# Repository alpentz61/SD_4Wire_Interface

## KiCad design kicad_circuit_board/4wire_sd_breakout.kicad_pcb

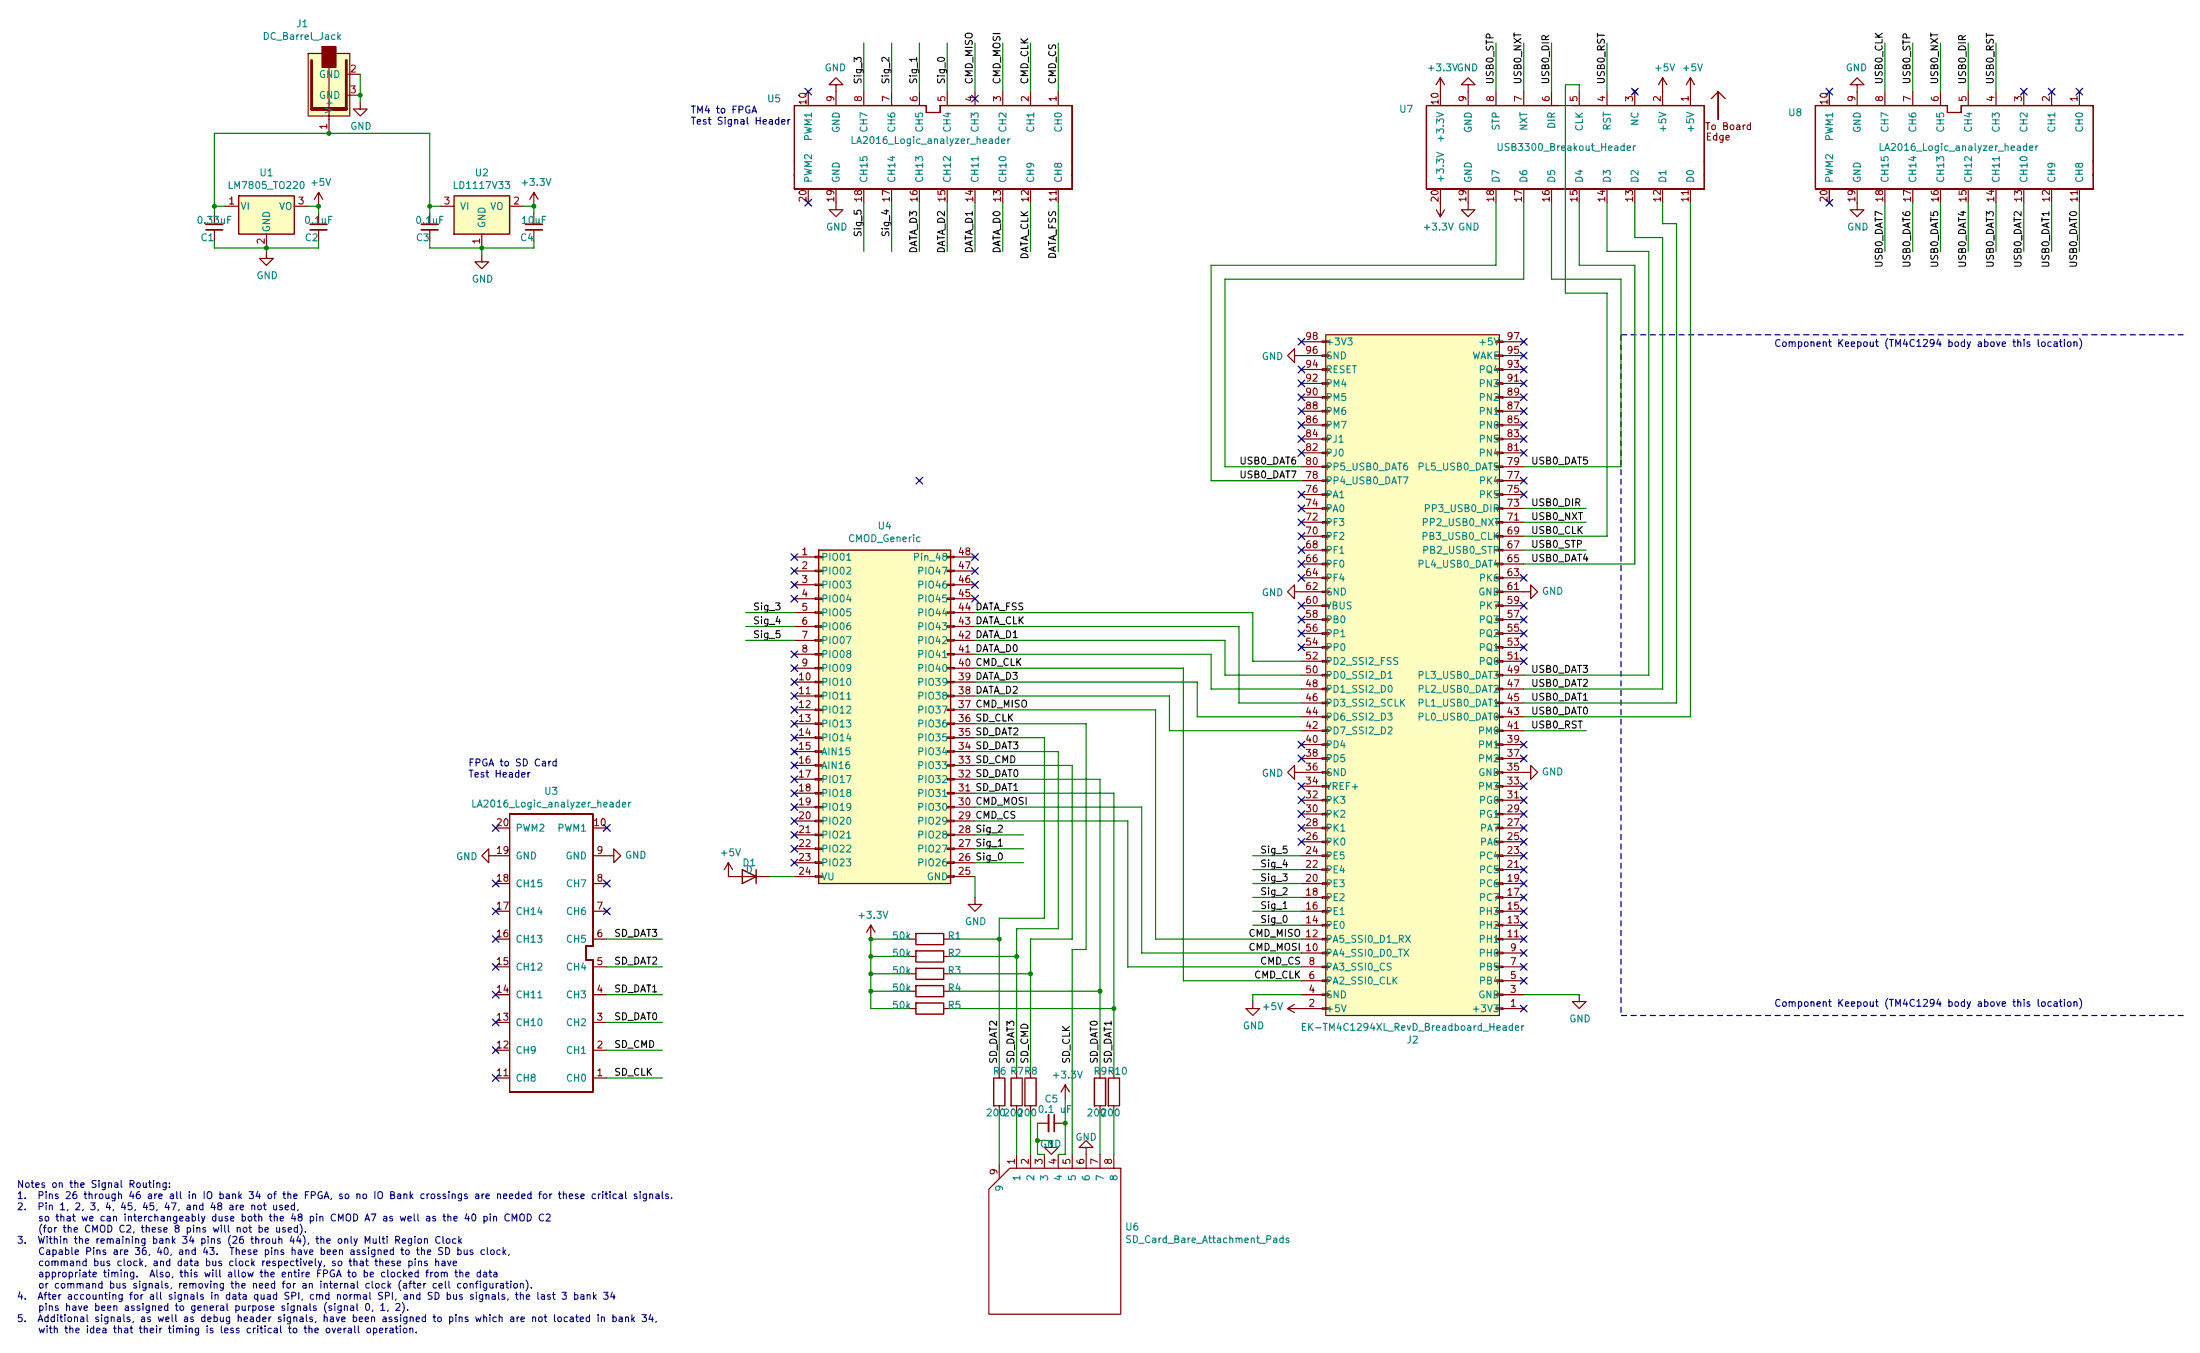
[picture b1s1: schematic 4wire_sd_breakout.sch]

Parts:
C1: 0.33uF; C_0603_1608Metric_Pad1.08x0.95mm_HandSolder
C2, C3: 0.1uF; C_0603_1608Metric_Pad1.08x0.95mm_HandSolder
C4: 10uF; C_0603_1608Metric_Pad1.08x0.95mm_HandSolder
C5: 0.1 uF; C_0603_1608Metric_Pad1.08x0.95mm_HandSolder
D1: D; D_A-405_P12.70mm_Horizontal
J1: DC_Barrel_Jack; DC_Barrel_Adapter
J2: EK-TM4C1294XL_RevD_Breadboard_Header
R1, R2, R3, R4, R5: 50k; R_0603_1608Metric_Pad0.98x0.95mm_HandSolder
R6, R7, R8, R9, R10: 200; R_0603_1608Metric_Pad0.98x0.95mm_HandSolder
U1: LM7805_TO220; TO-220-3_Vertical
U2: LD1117V33; TO-220-3_Vertical
U3, U5, U8: LA2016_Logic_analyzer_header; LA2016_Logic_Analyzer_Connector
U4: CMOD_Generic
U6: SD_Card_Bare_Attachment_Pads; SD_Card_Bare_Wire_Attachment_Pads
U7: USB3300_Breakout_Header; LA2016_Logic_Analyzer_Connector

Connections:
+3V3: C4.2, C5.1, R1.2, R2.2, R3.2, R4.2, R5.2, U2.2 (VO), U6.4, U7.10 (+3.3V), U7.20 (+3.3V)
+5V: C2.2, D1.2 (A), J2.2 (+5V), U1.3 (VO), U7.1 (+5V), U7.2 (+5V)
/CMD_CLK: J2.6 (PA2_SSI0_CLK), U4.40 (PIO40), U5.2 (CH1)
/CMD_CS: J2.8 (PA3_SSI0_CS), U4.29 (PIO29), U5.1 (CH0)
/CMD_MISO: J2.12 (PA5_SSI0_D1_RX), U4.37 (PIO37), U5.4 (CH3)
/CMD_MOSI: J2.10 (PA4_SSI0_D0_TX), U4.30 (PIO30), U5.3 (CH2)
/DATA_CLK: J2.46 (PD3_SSI2_SCLK), U4.43 (PIO43), U5.12 (CH9)
/DATA_D0: J2.48 (PD1_SSI2_D0), U4.41 (PIO41), U5.13 (CH10)
/DATA_D1: J2.50 (PD0_SSI2_D1), U4.42 (PIO42), U5.14 (CH11)
/DATA_D2: J2.42 (PD7_SSI2_D2), U4.38 (PIO38), U5.15 (CH12)
/DATA_D3: J2.44 (PD6_SSI2_D3), U4.39 (PIO39), U5.16 (CH13)
/DATA_FSS: J2.52 (PD2_SSI2_FSS), U4.44 (PIO44), U5.11 (CH8)
/SD_CLK: U3.1 (CH0), U4.36 (PIO36), U6.5
/SD_CMD: R3.1, R8.1, U3.2 (CH1), U4.33 (PIO33)
/SD_DAT0: R4.1, R9.1, U3.3 (CH2), U4.32 (PIO32)
/SD_DAT1: R5.1, R10.1, U3.4 (CH3), U4.31 (PIO31)
/SD_DAT2: R1.1, R6.1, U3.5 (CH4), U4.35 (PIO35)
/SD_DAT3: R2.1, R7.1, U3.6 (CH5), U4.34 (PIO34)
/Sig_0: J2.14 (PE0), U4.26 (PIO26), U5.5 (CH4)
/Sig_1: J2.16 (PE1), U4.27 (PIO27), U5.6 (CH5)
/Sig_2: J2.18 (PE2), U4.28 (PIO28), U5.7 (CH6)
/Sig_3: J2.20 (PE3), U4.5 (PIO05), U5.8 (CH7)
/Sig_4: J2.22 (PE4), U4.6 (PIO06), U5.17 (CH14)
/Sig_5: J2.24 (PE5), U4.7 (PIO07), U5.18 (CH15)
/USB0_CLK: J2.69 (PB3_USB0_CLK), U7.5 (CLK), U8.8 (CH7)
/USB0_DAT0: J2.43 (PL0_USB0_DAT0), U7.11 (D0), U8.11 (CH8)
/USB0_DAT1: J2.45 (PL1_USB0_DAT1), U7.12 (D1), U8.12 (CH9)
/USB0_DAT2: J2.47 (PL2_USB0_DAT2), U7.13 (D2), U8.13 (CH10)
/USB0_DAT3: J2.49 (PL3_USB0_DAT3), U7.14 (D3), U8.14 (CH11)
/USB0_DAT4: J2.65 (PL4_USB0_DAT4), U7.15 (D4), U8.15 (CH12)
/USB0_DAT5: J2.79 (PL5_USB0_DAT5), U7.16 (D5), U8.16 (CH13)
/USB0_DAT6: J2.80 (PP5_USB0_DAT6), U7.17 (D6), U8.17 (CH14)
/USB0_DAT7: J2.78 (PP4_USB0_DAT7), U7.18 (D7), U8.18 (CH15)
/USB0_DIR: J2.73 (PP3_USB0_DIR), U7.6 (DIR), U8.5 (CH4)
/USB0_NXT: J2.71 (PP2_USB0_NXT), U7.7 (NXT), U8.6 (CH5)
/USB0_RST: J2.41 (PM0), U7.4 (RST), U8.4 (CH3)
/USB0_STP: J2.67 (PB2_USB0_STP), U7.8 (STP), U8.7 (CH6)
GND: C1.1, C2.1, C3.1, C4.1, C5.2, J1.2 (GND), J1.3 (GND), J2.3 (GND), J2.4 (GND), J2.35 (GND), J2.36 (GND), J2.61 (GND), J2.62 (GND), J2.96 (GND), U1.2 (GND), U2.1 (GND), U3.9 (GND), U3.19 (GND), U4.25 (GND), U5.9 (GND), U5.19 (GND), U6.3, U6.6, U7.9 (GND), U7.19 (GND), U8.9 (GND), U8.19 (GND)
unnamed: C1.2, C3.2, J1.1 (V+), U1.1 (VI), U2.3 (VI)
unnamed: D1.1 (K), U4.24 (VU)
unnamed: R6.2, U6.9
unnamed: R7.2, U6.1
unnamed: R8.2, U6.2
unnamed: R9.2, U6.7
unnamed: R10.2, U6.8

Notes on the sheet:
TM4 to FPGA Test Signal Header
Notes on the Signal Routing: 1. Pins 26 through 46 are all in IO bank 34 of the FPGA, so no IO Bank crossings are needed for these critical signals. 2. Pin 1, 2, 3, 4, 45, 45, 47, and 48 are not used, so that we can interchangeably duse both the 48 pin CMOD A7 as well as the 40 pin CMOD C2 (for the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
FPGA to SD Card Test Header
Component Keepout (TM4C1294 body above this location)

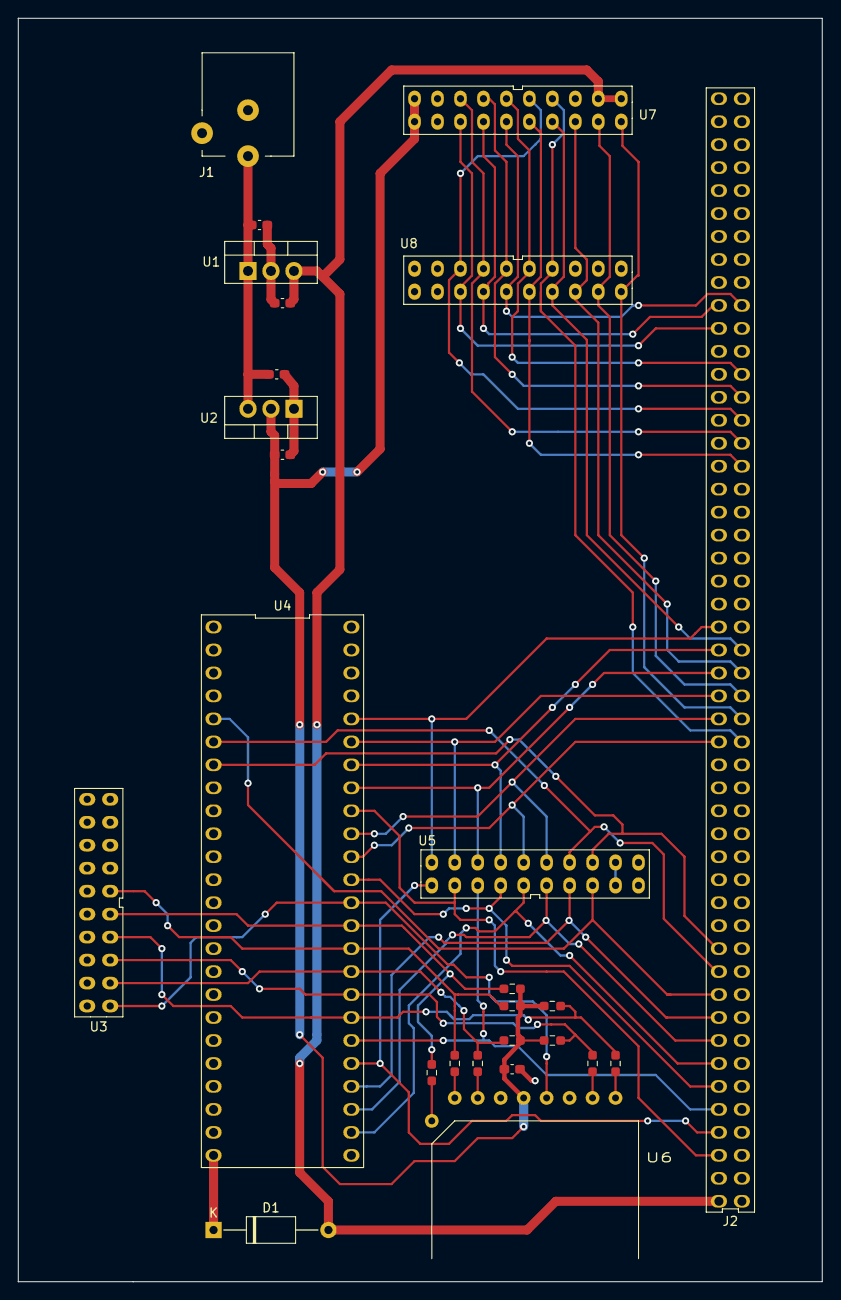
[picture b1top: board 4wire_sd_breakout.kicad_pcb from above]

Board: 2 copper layers, 88.9 x 139.7 mm, 26 parts (0 on the bottom side), 45 nets.

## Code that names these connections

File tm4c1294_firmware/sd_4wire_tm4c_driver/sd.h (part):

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#define CMD_SSI_PERIPH          SYSCTL_PERIPH_SSI0

// Pin mappings:
#define CMD_CLK_PIN             GPIO_PIN_2
#define CMD_CS_PIN              GPIO_PIN_3
#define CMD_MOSI_PIN            GPIO_PIN_4
#define CMD_MISO_PIN            GPIO_PIN_5

// Alternate Function Configurations for the Clock, MOSI, and MISO pins:
#define CMD_CLK_CFG             GPIO_PA2_SSI0CLK
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
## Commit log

2022-11-02 Performed some cleanup of the code since the initial commit, explicitly set the date in the file header comments in the new sd.c/h file to match the approximate date of the intial main.c creation (1/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
